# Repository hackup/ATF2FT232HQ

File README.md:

# ATF1504-FT232HQ Shield

This is a "hat" PCB that plugs onto an easily available FT232H board and provides a JTAG interface to ATF1504 CPLDs. It allows those ICs to be programmed and even to be reset when their JTAG interface has been disabled. There is also no warranty whatsoever. **USE AT YOUR OWN RISK!**.

See my [blog post](https://www.hackup.net/2020/01/erasing-and-programming-the-atf1504-cpld/) for more details.

## License
[
](http://creativecommons.org/licenses/by-nc-sa/4.0/)

This work is licensed under a
[Creative Commons Attribution-NonCommercial-ShareAlike 4.0 International License](http://creativecommons.org/licenses/by-nc-sa/4.0/).

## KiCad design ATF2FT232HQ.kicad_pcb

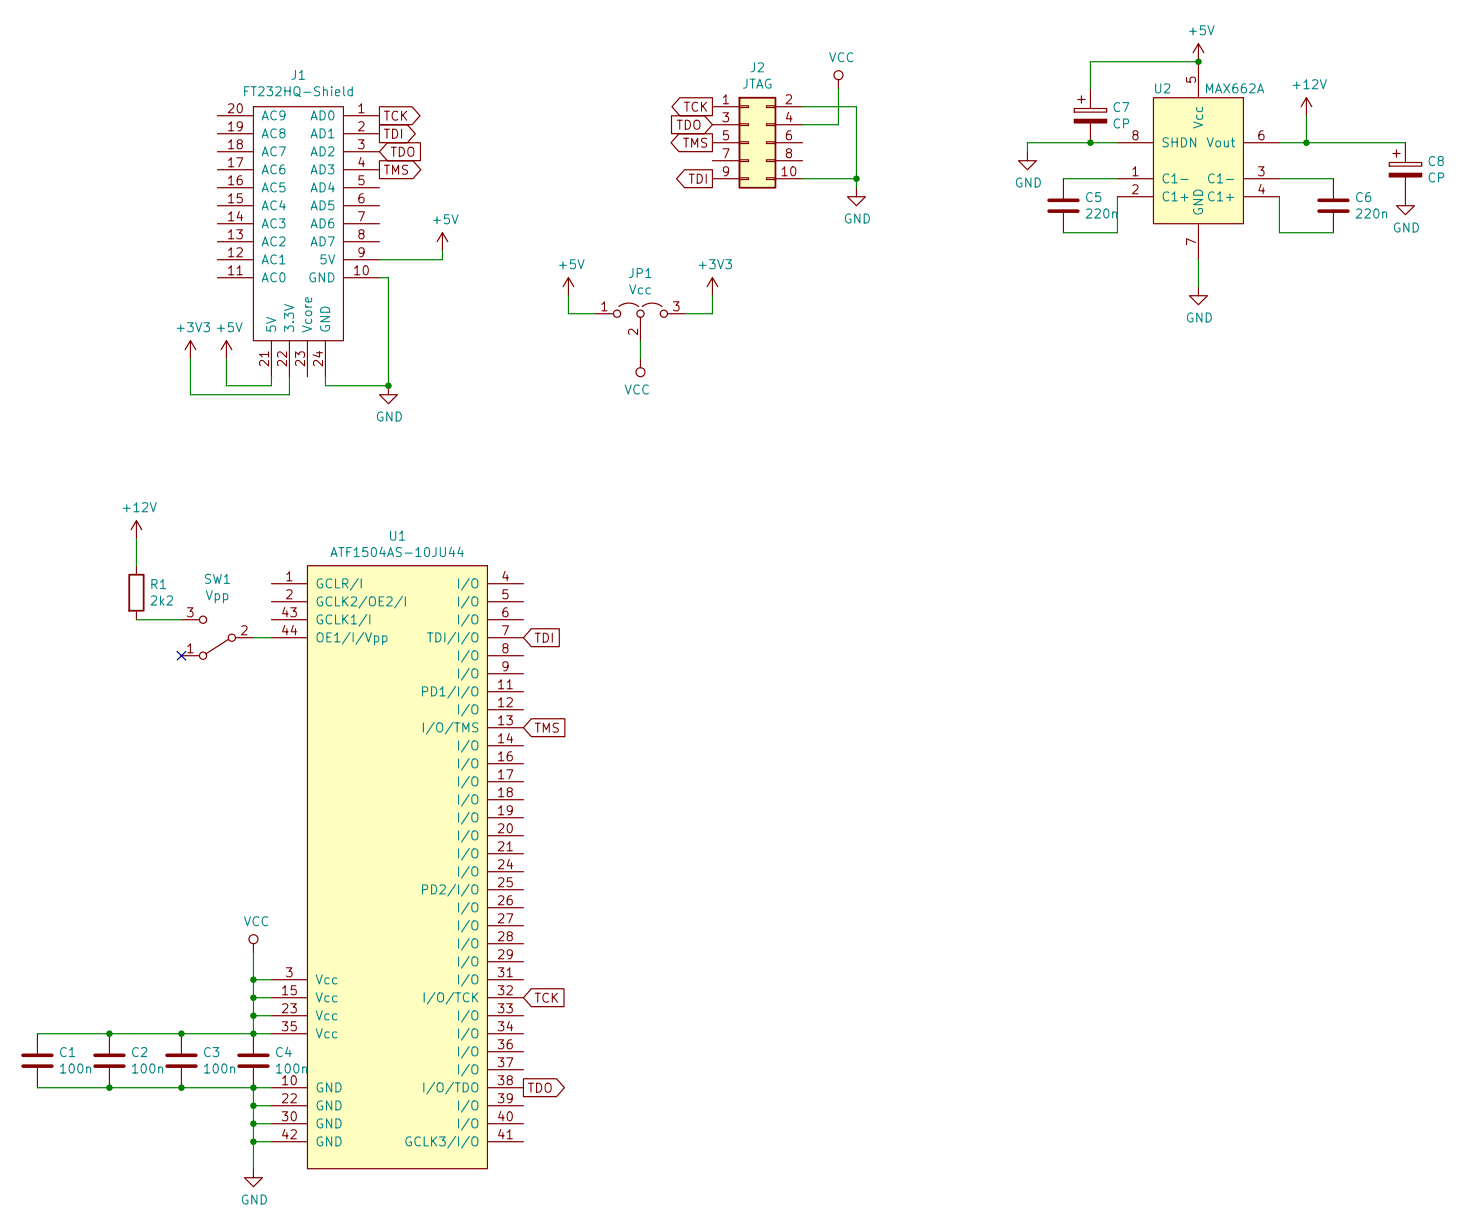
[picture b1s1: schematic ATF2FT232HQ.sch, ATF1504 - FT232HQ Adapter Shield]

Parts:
C1, C2, C3, C4: 100n; C_0805_2012Metric_Pad1.15x1.40mm_HandSolder
C5, C6: 220n; C_0805_2012Metric_Pad1.15x1.40mm_HandSolder
C7, C8: CP; CP_EIA-3216-18_Kemet-A_Pad1.58x1.35mm_HandSolder
J1: FT232HQ-Shield
J2: JTAG; PinHeader_2x05_P2.54mm_Vertical
JP1: Vcc; PinHeader_1x03_P2.54mm_Vertical
R1: 2k2; R_0805_2012Metric_Pad1.15x1.40mm_HandSolder
SW1: Vpp; PinHeader_1x03_P2.54mm_Vertical
U1: ATF1504AS-10JU44; PLCC-44_THT-Socket
U2: MAX662A; SOIC-8_3.9x4.9mm_P1.27mm

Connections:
+3V3: J1.22 (3.3V), JP1.3 (B)
+5V: C7.1, J1.9 (5V), J1.21 (5V), JP1.1 (A), U2.5 (Vcc)
+12V: C8.1, R1.1, U2.6 (Vout)
GND: C1.2, C2.2, C3.2, C4.2, C7.2, C8.2, J1.10 (GND), J1.24 (GND), J2.2, J2.10, U1.10 (GND), U1.22 (GND), U1.30 (GND), U1.42 (GND), U2.7 (GND), U2.8 (SHDN)
unnamed: C5.1, U2.1 (C1-)
unnamed: C5.2, U2.2 (C1+)
unnamed: C6.1, U2.3 (C1-)
unnamed: C6.2, U2.4 (C1+)
unnamed: R1.2, SW1.3 (C)
unnamed: SW1.2 (B), U1.44 (OE1/I/Vpp)
TCK: J1.1 (AD0), J2.1, U1.32 (I/O/TCK)
TDI: J1.2 (AD1), J2.9, U1.7 (TDI/I/O)
TDO: J1.3 (AD2), J2.3, U1.38 (I/O/TDO)
TMS: J1.4 (AD3), J2.5, U1.13 (I/O/TMS)
VCC: C1.1, C2.1, C3.1, C4.1, J2.4, JP1.2 (C), U1.3 (Vcc), U1.15 (Vcc), U1.23 (Vcc), U1.35 (Vcc)

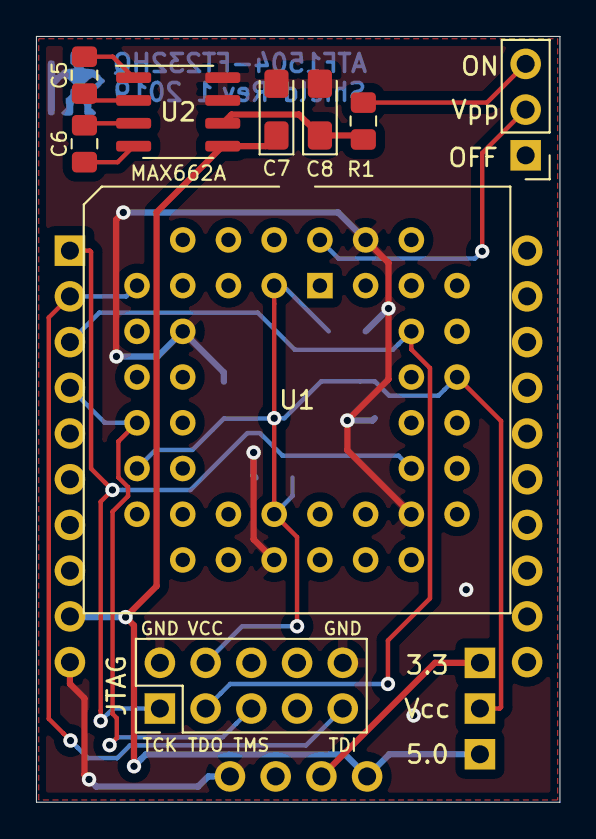
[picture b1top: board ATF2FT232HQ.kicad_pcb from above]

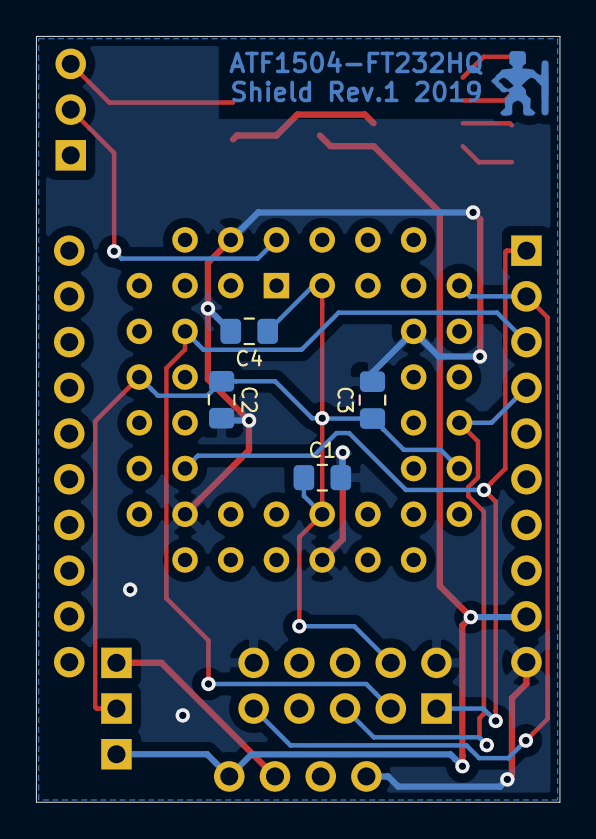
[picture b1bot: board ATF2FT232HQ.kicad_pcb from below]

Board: 2 copper layers, 29.1 x 42.5 mm, 15 parts (4 on the bottom side), 15 nets.

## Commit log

2019-11-17 Initial import of JTAG adapter.
2019-11-19 Started routing.
2019-11-20 First routing completed.
2019-11-20 Moved components to the top.
2019-11-20 Labeled and tagged.
2019-11-20 Updated MAX662 footprint.
2019-11-20 Prepared Gerber export.
2020-01-21 Fix.
2020-01-21 Added readme and schematics.
2021-06-12 Fixed typo.
